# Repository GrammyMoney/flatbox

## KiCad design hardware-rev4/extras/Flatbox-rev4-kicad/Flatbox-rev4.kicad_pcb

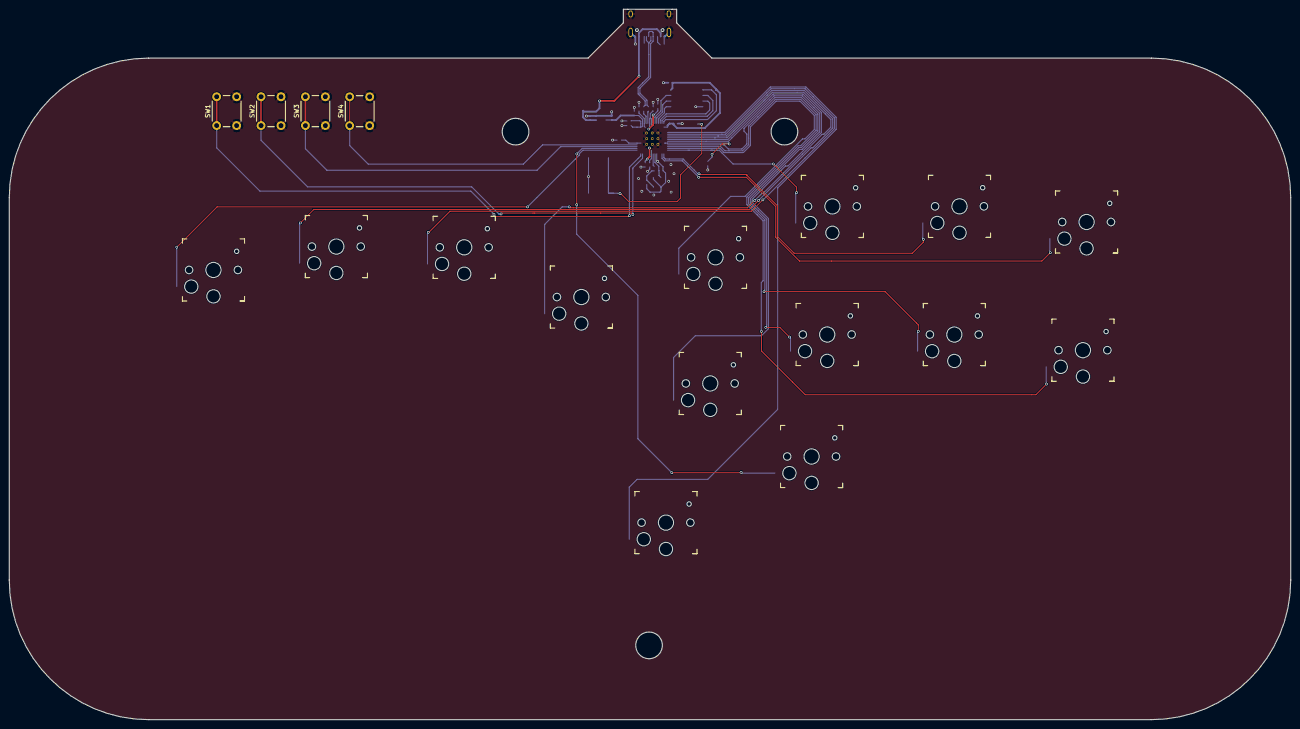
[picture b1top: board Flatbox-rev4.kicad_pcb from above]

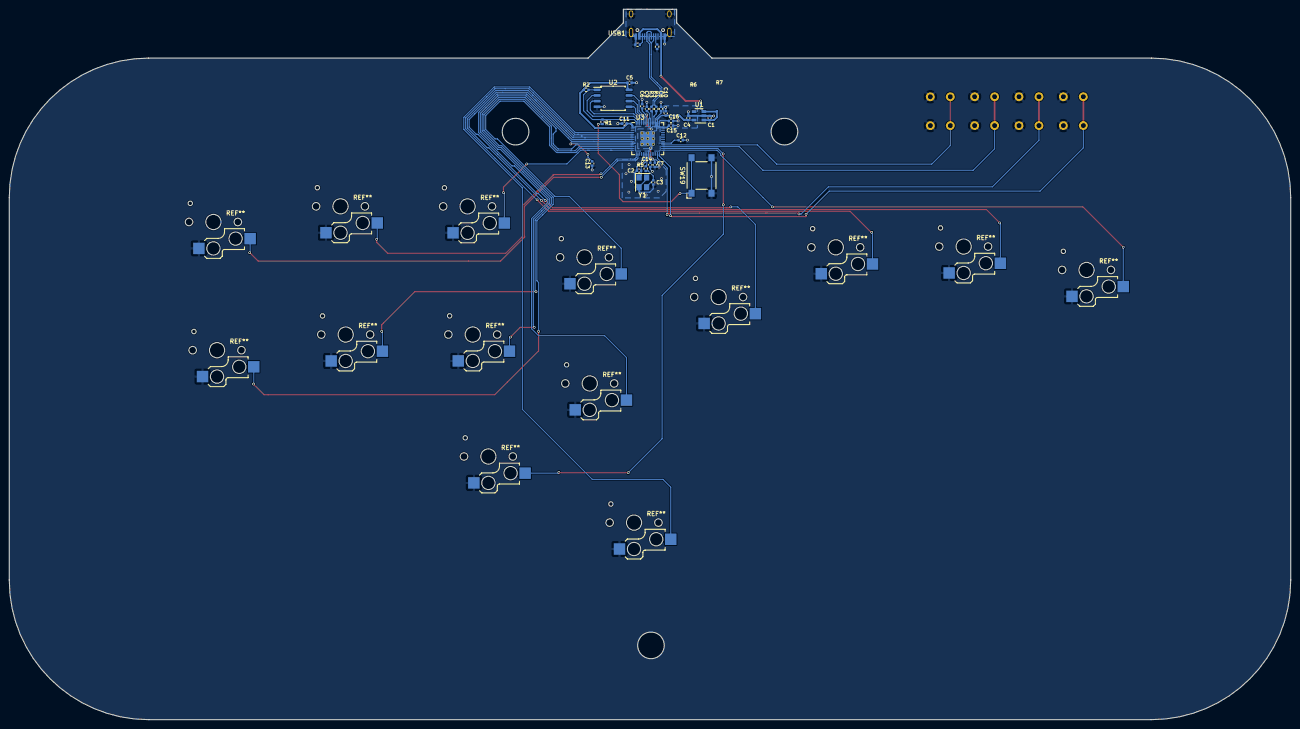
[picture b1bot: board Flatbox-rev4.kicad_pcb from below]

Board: 2 copper layers, 288.8 x 160.1 mm, 33 parts (29 on the bottom side), 24 nets.

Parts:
C1, C4, C8, C10: 1u; C_0402_1005Metric
C2, C3: 30p; C_0402_1005Metric
C5, C6, C7, C9, C11, C12, C13, C14, C15, C16: 100n; C_0402_1005Metric
R1, R5: 1k; R_0402_1005Metric
R2: 10k; R_0402_1005Metric
R3, R4: 27; R_0402_1005Metric
R6, R7: 5.1k; R_0402_1005Metric
SW1, SW2, SW3, SW4: SW_Push; SW_PUSH_6mm_H5mm
SW19: SW_Push; SW_SPST_Omron_B3FS-100xP
U1: TLV73333PDBV; SOT-23-5
U2: W25Q128JVS; SOIC-8_5.23x5.23mm_P1.27mm
U3: RP2040; RP2040-QFN-56
USB1: HRO-TYPE-C-31-M-12; HRO-TYPE-C-31-M-12-Assembly
Y1: Crystal_GND24; Crystal_SMD_3225-4Pin_3.2x2.5mm

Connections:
+1V1: C6.1, C7.1, C8.1, U3.23, U3.45, U3.50
+3V3: C4.1, C5.1, C9.1, C10.1, C11.1, C12.1, C13.1, C14.1, C15.1, C16.1, R2.1, U1.5, U2.8, U3.1, U3.10, U3.22, U3.33, U3.42, U3.43, U3.44, U3.48, U3.49
+5V: C1.1, U1.1, U1.3, USB1.2, USB1.11
CAPTURE: SW4.1, U3.32
D+: R3.1, USB1.6, USB1.8
D-: R4.1, USB1.5, USB1.7
GND: C1.2, C2.1, C3.2, C4.2, C5.2, C6.2, C7.2, C8.2, C9.2, C10.2, C11.2, C12.2, C13.2, C14.2, C15.2, C16.2, R6.2, R7.2, SW1.2, SW2.2, SW3.2, SW4.2, SW19.1, U1.2, U2.4, U3.19, U3.57, USB1.1, USB1.12, USB1.13, Y1.2, Y1.4
HOME: SW3.1, U3.31
unnamed: C3.1, R5.1, Y1.3
unnamed: R1.2, SW19.2
unnamed: R3.2, U3.47
unnamed: R4.2, U3.46
unnamed: R6.1, USB1.10
unnamed: R7.1, USB1.4
QSPI_SCLK: U2.6, U3.52
QSPI_SD0: U2.5, U3.53
QSPI_SD1: U2.2, U3.55
QSPI_SD2: U2.3, U3.54
QSPI_SD3: U2.7, U3.51
QSPI_SS: R1.1, R2.2, U2.1, U3.56
SELECT: SW2.1, U3.27
START: SW1.1, U3.28
XIN: C2.2, U3.20, Y1.1
XOUT: R5.2, U3.21

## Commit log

2023-11-10 modified for GRAM Slim package
2023-11-10 removed clutter
